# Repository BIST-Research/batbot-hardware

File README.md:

# batbot-hardware
schematics and pcbs for the batbot

## batbot-6.5 wiring diagram

## Adafruit itsybitsy M4 pinout

## Grandcentral M4 pinout

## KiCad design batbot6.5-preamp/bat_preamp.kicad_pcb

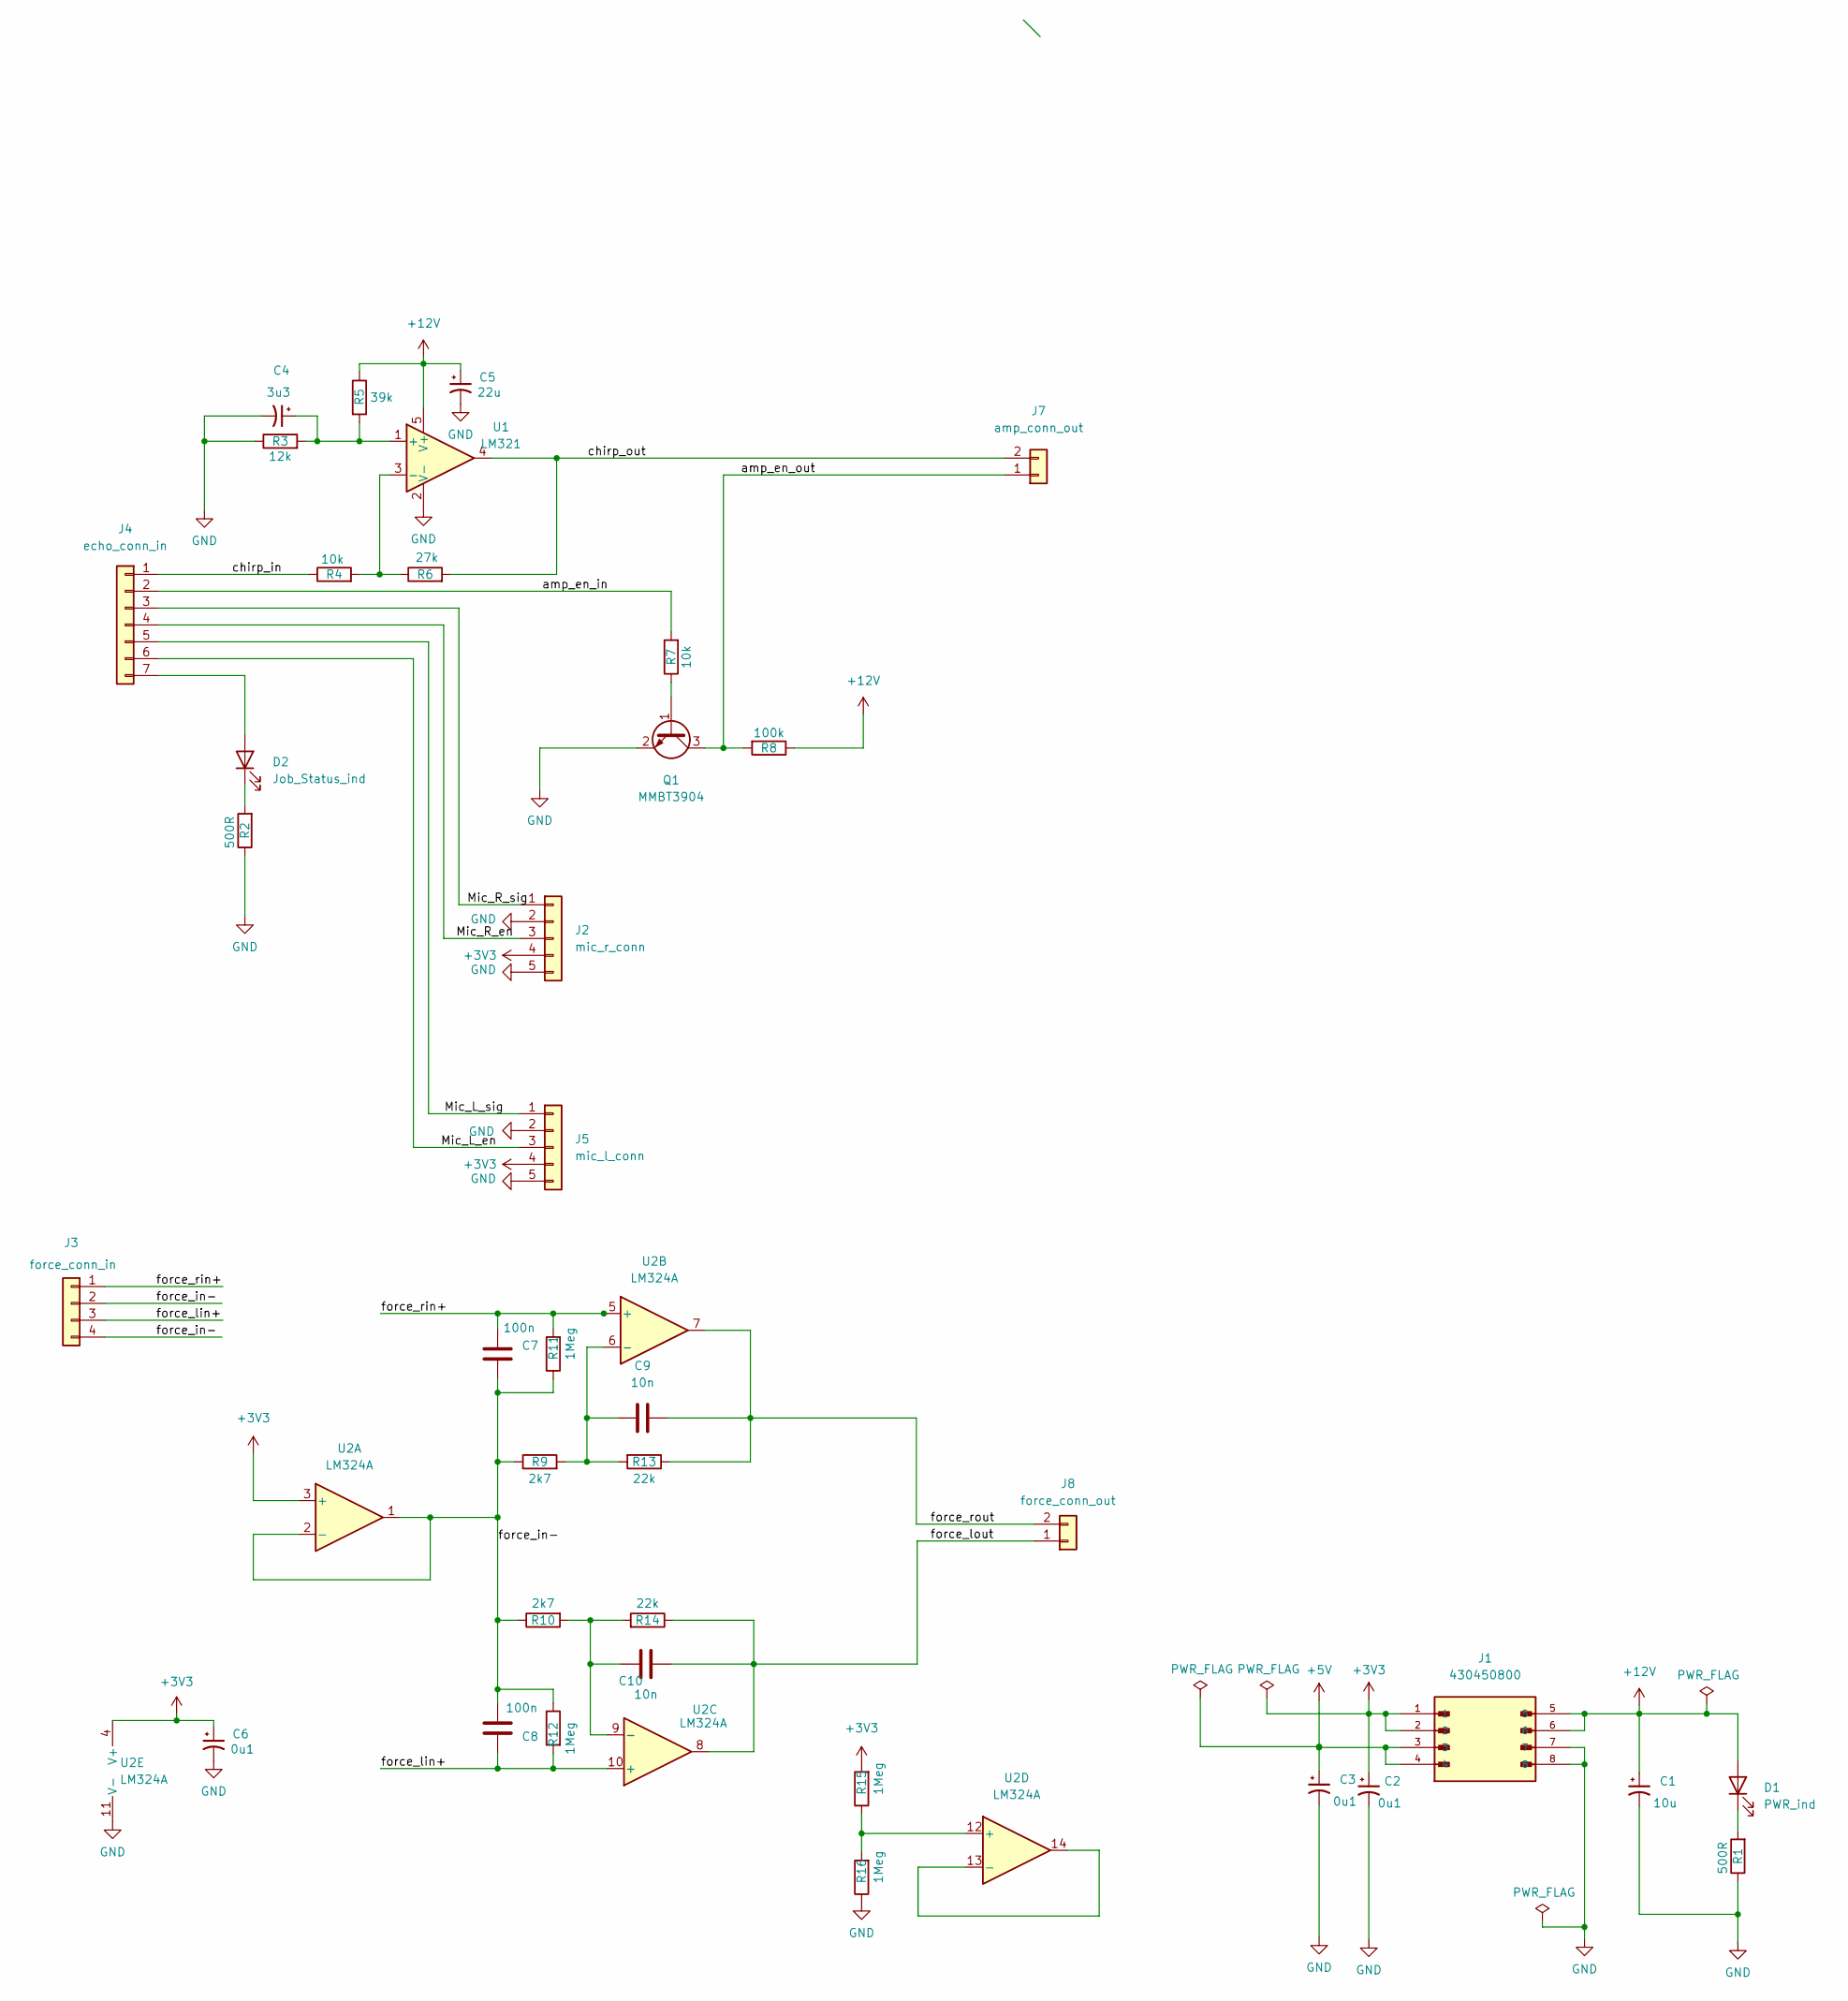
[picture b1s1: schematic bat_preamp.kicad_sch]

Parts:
C1: 10u; CP_EIA-3528-21_Kemet-B_Pad1.50x2.35mm_HandSolder
C2, C3: 0u1; CP_EIA-3216-18_Kemet-A_Pad1.58x1.35mm_HandSolder
C4: 3u3; CP_EIA-3216-18_Kemet-A_Pad1.58x1.35mm_HandSolder
C5: 22u; CP_EIA-3216-18_Kemet-A_Pad1.58x1.35mm_HandSolder
C6: 0u1; CP_EIA-6032-28_Kemet-C_Pad2.25x2.35mm_HandSolder
C7, C8: 100n; C_0402_1005Metric_Pad0.74x0.62mm_HandSolder
C9, C10: 10n; C_0402_1005Metric_Pad0.74x0.62mm_HandSolder
D1: PWR_ind; LED_0603_1608Metric_Pad1.05x0.95mm_HandSolder
D2: Job_Status_ind; LED_0603_1608Metric_Pad1.05x0.95mm_HandSolder
J1: 430450800; MOLEX_430450800; PARTREV G
J2: mic_r_conn; JST_XH_B5B-XH-A_1x05_P2.50mm_Vertical
J3: force_conn_in; JST_XH_B4B-XH-A_1x04_P2.50mm_Vertical
J4: echo_conn_in; JST_XH_B7B-XH-A_1x07_P2.50mm_Vertical
J5: mic_l_conn; JST_XH_B5B-XH-A_1x05_P2.50mm_Vertical
J7: amp_conn_out; JST_XH_B2B-XH-A_1x02_P2.50mm_Vertical
J8: force_conn_out; JST_XH_B2B-XH-A_1x02_P2.50mm_Vertical
Q1: MMBT3904; SOT-23
R1, R2: 500R; R_1206_3216Metric_Pad1.30x1.75mm_HandSolder
R3: 12k; R_0603_1608Metric_Pad0.98x0.95mm_HandSolder
R4: 10k; R_1206_3216Metric_Pad1.30x1.75mm_HandSolder
R5: 39k; R_0603_1608Metric_Pad0.98x0.95mm_HandSolder
R6: 27k; R_1206_3216Metric_Pad1.30x1.75mm_HandSolder
R7: 10k; R_0603_1608Metric_Pad0.98x0.95mm_HandSolder
R8: 100k; R_1206_3216Metric_Pad1.30x1.75mm_HandSolder
R9, R10: 2k7; R_0603_1608Metric_Pad0.98x0.95mm_HandSolder
R11, R12, R15, R16: 1Meg; R_0603_1608Metric_Pad0.98x0.95mm_HandSolder
R13, R14: 22k; R_0603_1608Metric_Pad0.98x0.95mm_HandSolder
U1: LM321; SOT-23-5
U2: LM324A; SOIC-14_3.9x8.7mm_P1.27mm

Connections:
+3V3: C2.1, C6.1, J1.1, J1.2, J2.4, J5.4, R15.2, U2.3 (+), U2.4 (V+)
+5V: C3.1, J1.3, J1.4
+12V: C1.1, C5.1, D1.2 (A), J1.5, J1.6, R5.1, R8.1, U1.5 (V+)
/Mic_L_en: J4.6, J5.3
/Mic_L_sig: J4.5, J5.1
/Mic_R_en: J2.3, J4.4
/Mic_R_sig: J2.1, J4.3
/amp_en_in: J4.2, R7.2
/amp_en_out: J7.1, Q1.3 (C), R8.2
/chirp_in: J4.1, R4.1
/chirp_out: J7.2, R6.2, U1.4
/force_in-: C7.2, C8.2, J3.2, J3.4, R9.1, R10.1, R11.1, R12.1, U2.1, U2.2 (-)
/force_lin+: C8.1, J3.3, R12.2, U2.10 (+)
/force_lout: C10.2, J8.1, R14.1, U2.8
/force_rin+: C7.1, J3.1, R11.2, U2.5 (+)
/force_rout: C9.2, J8.2, R13.1, U2.7
GND: C1.2, C2.2, C3.2, C4.2, C5.2, C6.2, J1.7, J1.8, J2.2, J2.5, J5.2, J5.5, Q1.2 (E), R1.1, R2.1, R3.1, R16.1, U1.2 (V-), U2.11 (V-)
unnamed: C4.1, R3.2, R5.2, U1.1 (+)
unnamed: C9.1, R9.2, R13.2, U2.6 (-)
unnamed: C10.1, R10.2, R14.2, U2.9 (-)
unnamed: D1.1 (K), R1.2
unnamed: D2.1 (K), R2.2
unnamed: D2.2 (A), J4.7
unnamed: Q1.1 (B), R7.1
unnamed: R4.2, R6.1, U1.3 (-)
unnamed: R15.1, R16.2, U2.12 (+)
unnamed: U2.13 (-), U2.14

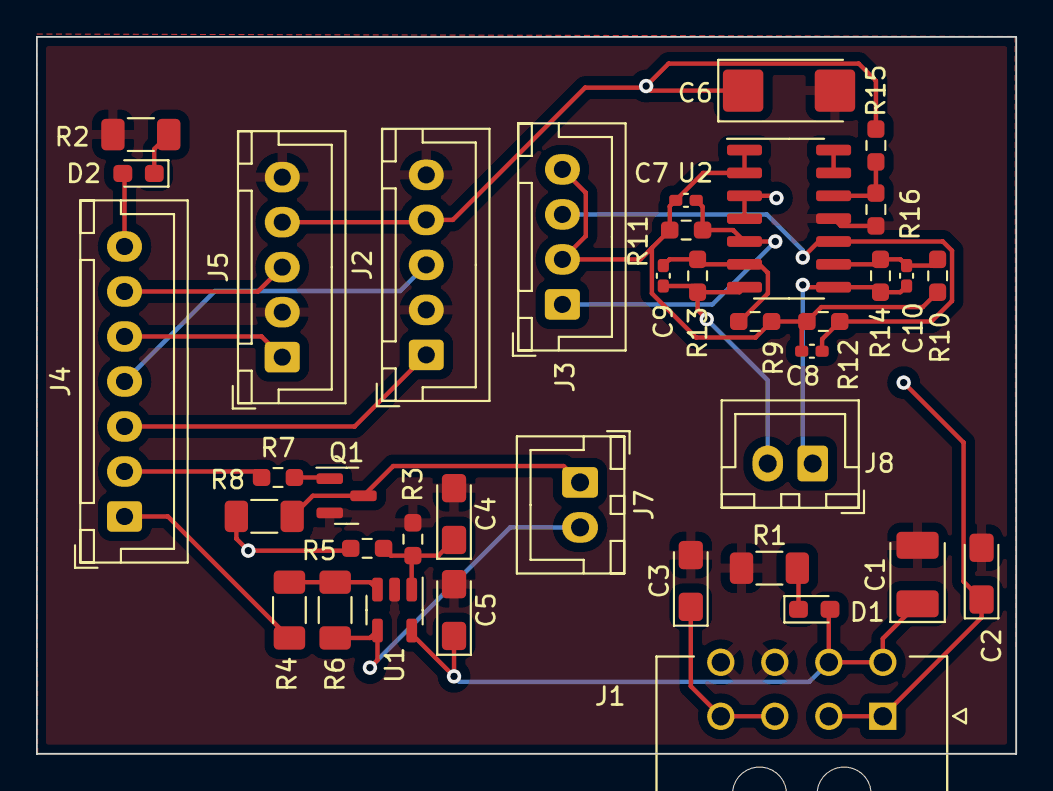
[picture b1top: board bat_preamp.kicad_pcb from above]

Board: 2 copper layers, 54.4 x 39.8 mm, 38 parts (0 on the bottom side), 27 nets.

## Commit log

2023-09-06 pushing docs/shems/pcbs
2023-09-06 update wd to jpg
